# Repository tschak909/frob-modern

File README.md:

# frob-modern: Frob2354

A modern, register-compatible replacement for the **FROB** (Frobco, 1982),
the Apple II card for Atari 2600 development.  The original is 22 74LS
packages and two M58725P 2K x 8 SRAMs; parts that are hard to find today, and
whose modern substitutes make reconstructed boards erratic.  Frob2354 is one
**RP2354B** (RP2350B + 2 MB flash), four 74LVC245A bus buffers, two single
gates and a 3.3 V LDO on an Apple II slot card, with the original's **DIP-24
cable socket** so the existing FROB cable and 2600 cartridge adapter plug
straight in, and the original **register map**, so the existing FROB
software runs unchanged.

```
hardware/   KiCad 10 project (generated from tools/design.py) + JLCPCB outputs
firmware/   Pico SDK firmware: the FROB's RAM and registers, both buses
test/       host tests of the register semantics (the firmware's own code)
```

## Why an RP2354B and not an RP2040

The Apple bus and the 2600 bus run at the same time and are asynchronous to
each other (the 2600 executes from the FROB RAM while the Apple polls the
mailbox), so they cannot share pins.  Apple A0-A7, D0-D7, R/W, /IOSEL,
/DEVSEL, PHI0, /RES plus 2600 A0-A11, /CE, D0-D7 and the buffer controls is
46 GPIOs; the RP2040 has 30.  The RP2350B has 48, 5 V-tolerant pads on
GPIO0-39, the same SDK, and the RP2354B variant carries its flash in the
package.

## The card

* **Apple side:** A0-A7, R/W, /IOSEL, /DEVSEL, PHI0, /RES straight into the
  RP's 5 V-tolerant pads (GP8-20).  D0-D7 through a 74LVC245A whose DIR is
  R/W and whose /OE is `(/IOSEL & /DEVSEL) | A2_DOE` in hardware: the card
  cannot drive the Apple bus outside its own slot cycles.  INT and DMA
  daisy chains are passed through.
* **2600 side (J2, original FROB pin-out):** every cable signal goes through
  a 74LVC245A on the card's 3.3 V (Ioff, 5 V-tolerant), because the 2600 is
  powered separately; 100k pull-downs keep the address inputs defined with
  the cable unplugged.  The data buffer's /OE is `/CE | V_DOE` in hardware.
* **Power:** slot +5 V through a P-FET, USB VBUS through a Schottky, AP2112K
  to 3.3 V.  USB-C is for firmware updates (BOOTSEL) and bench power and can
  never back-feed the Apple.
* 6-layer, 1.6 mm, ENIG with hard-gold bevelled fingers.  All SMD on the top
  side; the DIP-24 socket is hand-soldered (JLCPCB stocks no 24-pin 0.6 in
  socket).

## Documentation

* `firmware/README.md`: register map, how each bus is served, timing
  budget, flashing, bring-up checklist.
* `hardware/README.md`: how the board files are generated and checked, the
  fab outputs, JLCPCB order settings.
* Original hardware, software and manuals: retroabandon/apple2-re `frob/`
  (https://gitlab.com/retroabandon/apple2-re/-/tree/main/frob); MAME's
  `a2frob` device emulates the original.

## Status

Rev0: schematic, 6-layer layout, JLCPCB outputs (`hardware/exports/jlcpcb/`)
and firmware generated and checked -- ERC 0, DRC 0 errors / 0 unconnected /
0 schematic-parity, netlist vs firmware pin map 159/159, host tests of the
register semantics 4144/4144, kicad-happy review triaged in
`hardware/docs/design-review-rev0.md`.
**No board has been built yet** -- see the bring-up checklist in
`firmware/README.md`.

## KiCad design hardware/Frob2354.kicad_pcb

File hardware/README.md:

# Frob2354 hardware

KiCad 10 project.  **Every KiCad file here is generated** from
`tools/design.py` (parts, values, MPN/LCSC codes, every pin's net) and
`tools/placement.py`; edit those and regenerate, not the schematic or board.
The generator toolchain is FujiNet-NES-Rev0's (fujinet-hardware), adapted to
a 6-layer Apple II card.

## Rebuild

Needs KiCad 10 (`kicad-cli` + the `pcbnew` Python module), Python 3 + numpy,
Java and Freerouting 2.4.1 (`~/.local/share/freerouting/freerouting-2.4.1.jar`).

```sh
tools/build_all.sh            # schematic, ERC, netlist checks, BOM, PDF
LAYOUT=1 tools/build_all.sh   # + placement, routing, DRC, gerbers, CPL, renders
```

| step | tool |
|---|---|
| symbols | `harvest_symbols.py` -> `tools/symcache.sexpr` (stock KiCad symbols, flattened) |
| footprints | `make_a2edge_fp.py` (Apple 50-pin edge); the rest are stock KiCad / FujiNet-NES footprints in `Frob2354.pretty` |
| schematic | `gen_sch.py` + `sch_layout.py` + `sch_route.py`: a block-diagram root (Apple slot -> RP2354B -> 2600 cable, power below, joined by buses) and four wired sheets -- parts placed by hand in `sch_layout.py`, every connection drawn by an orthogonal router, parallel buses as KiCad buses, rails as power symbols, signals that leave a sheet as hierarchical labels |
| connectivity | `compare_netlists.py tools/reference-netlist.xml`: the drawing produces exactly the reference connectivity (the netlist only changes when `design.py` does; refresh the reference then) |
| checks | `kicad-cli sch erc`; `check_nets.py`: the netlist against `../firmware/src/frob_pins.h`, the Apple slot pin-out, the original FROB J2 pin-out and the buffer-enable logic -- independent of `design.py` |
| board | `gen_pcb.py` (outline, placement, finger stubs, plane fan-out, RP core copper, zones), `finish_route.py --lock` (RP core corner), `finish_route.py --nets=...` (slot fingers), `route.py` (Freerouting), `via_in_pad.py` (boxed-in RP pins), `drc_fix.py`, `finish_route.py`, `tidy_tracks.py`, `stitch_gnd.py` |
| outputs | `export.py`: BOM, JLCPCB BOM + CPL, gerbers + drill zip, schematic PDF, renders |

## Board

* Apple II peripheral card in the original FROB card's frame (the
  reverse-engineered `a2board.kicad_pcb`): the same 65.4 x 7.62 mm tab, the
  same rear edge; the front is cut back (85.9 x 69.85 mm body).
* Fingers: 0.1 in pitch, 1.52 x 7.32 mm, pins 1-25 on the component side
  (pin 1 toward the front of the computer), 26-50 behind them on the solder
  side, pin N opposite 51-N.  `check_nets.py` asserts this from the footprint.
* Stack-up (FujiNet-NES-Rev0's): F.Cu signals + GND pour / In1 GND / In2 + In3
  signals / In4 +3V3 (DVDD island under the RP2354B core) / B.Cu signals + GND
  pour.  A 4-layer version (two signal layers) was tried first: Freerouting and
  the finisher left ~16 connections open around the RP2354B's 0.4 mm pin rows.
* J2 (FROB cable): DIP-24 0.6 in socket, original pin-out (2732 EPROM order;
  /CE = A12 inverted on the cable adapter, /OE grounded there, pin 24 open).

## Ordering at JLCPCB

`exports/jlcpcb/`: `Frob2354-gerbers.zip`, `BOM-JLCPCB.csv`, `CPL-JLCPCB.csv`.

* PCB: 6 layers, 1.6 mm, **ENIG**, **gold fingers: yes**, **bevelled edge
  (45 deg): yes**, impedance control not needed.  **Via covering: epoxy
  filled and capped (via-in-pad)** -- ten RP2354B signal pads carry a
  0.25/0.15 mm via (`tools/via_in_pad.py`); JLCPCB's 6-layer process includes it.
* Assembly: top side, Economic or Standard; every assembled part has an
  LCSC code (the extended ones: RP2354B, 74LVC245A, 74LVC1G0832, 74LVC1G32,
  AP2112K, AO3401A, USB-C, inductor, crystal, switches).  Check the
  placement preview for pin 1 of U1-U8, the USB-C and the diodes.
* Hand-solder J2: a 24-pin 0.6 in DIP socket (e.g. Mill-Max
  110-43-624-41-001000, or any turned-pin socket).

## Files

| | |
|---|---|
| `Frob2354.kicad_pro/.kicad_sch/.kicad_pcb` | the project (generated) |
| `apple.kicad_sch`, `mcu.kicad_sch`, `vcs.kicad_sch`, `power.kicad_sch` | the four sheets (Apple slot, RP2354B, 2600 cable, power / USB) |
| `tools/relink_pcb.py` | renames board nets / re-points footprints after a schematic redraw, copper untouched (used once, when the drawing became hierarchical: local nets gained sheet paths such as `/mcu/XIN`) |
| `Frob2354.pretty`, `Frob2354.kicad_sym` | project footprints / symbols |
| `datasheets/` | datasheets used in the review (`manifest.json`; PDFs not committed) |
| `docs/` | schematic PDF, layout SVGs, renders |

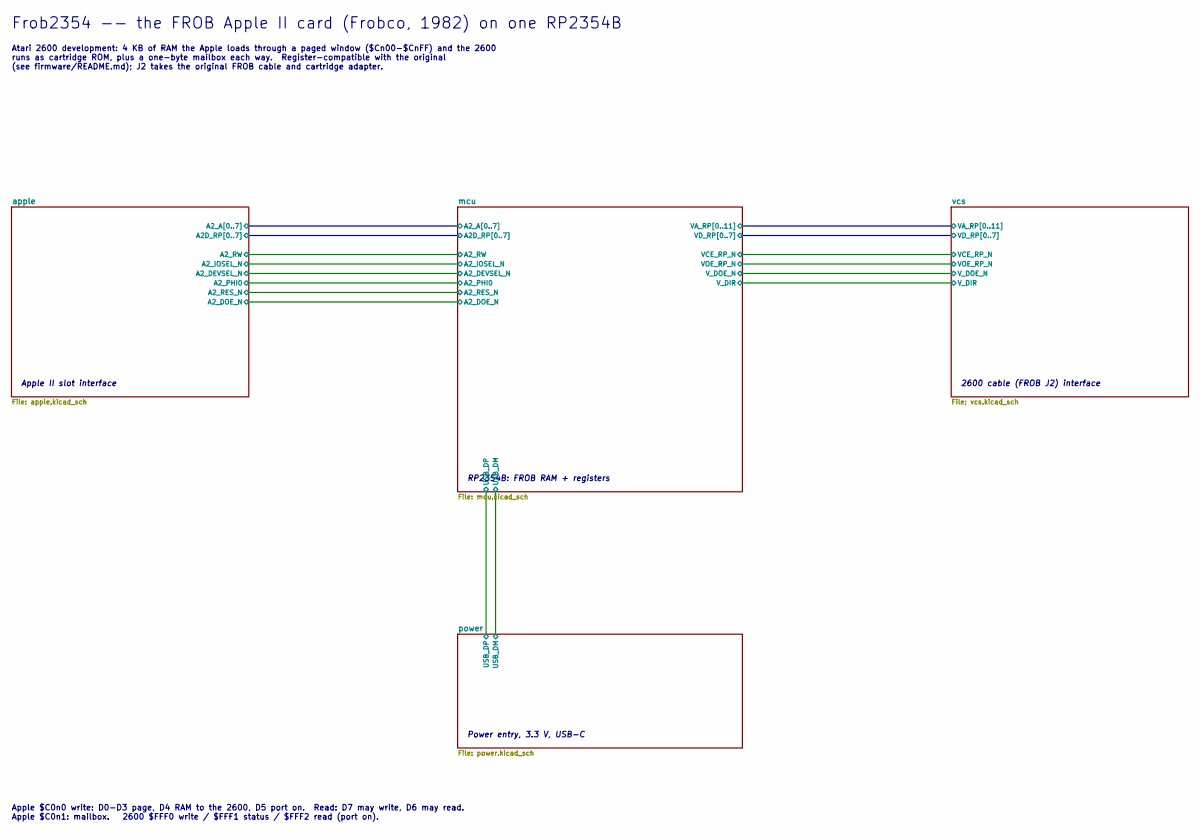
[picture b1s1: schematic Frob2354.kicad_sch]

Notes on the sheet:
Apple II slot interface
RP2354B: FROB RAM + registers
2600 cable (FROB J2) interface
Power entry, 3.3 V, USB-C
Frob2354 -- the FROB Apple II card (Frobco, 1982) on one RP2354B
Atari 2600 development: 4 KB of RAM the Apple loads through a paged window ($Cn00-$CnFF) and the 2600 runs as cartridge ROM, plus a one-byte mailbox each way. Register-compatible with the original (see firmware/README.md); J2 takes the original FROB cable and cartridge adapter.
Apple $C0n0 write: D0-D3 page, D4 RAM to the 2600, D5 port on. Read: D7 may write, D6 may read. Apple $C0n1: mailbox. 2600 $FFF0 write / $FFF1 status / $FFF2 read (port on).

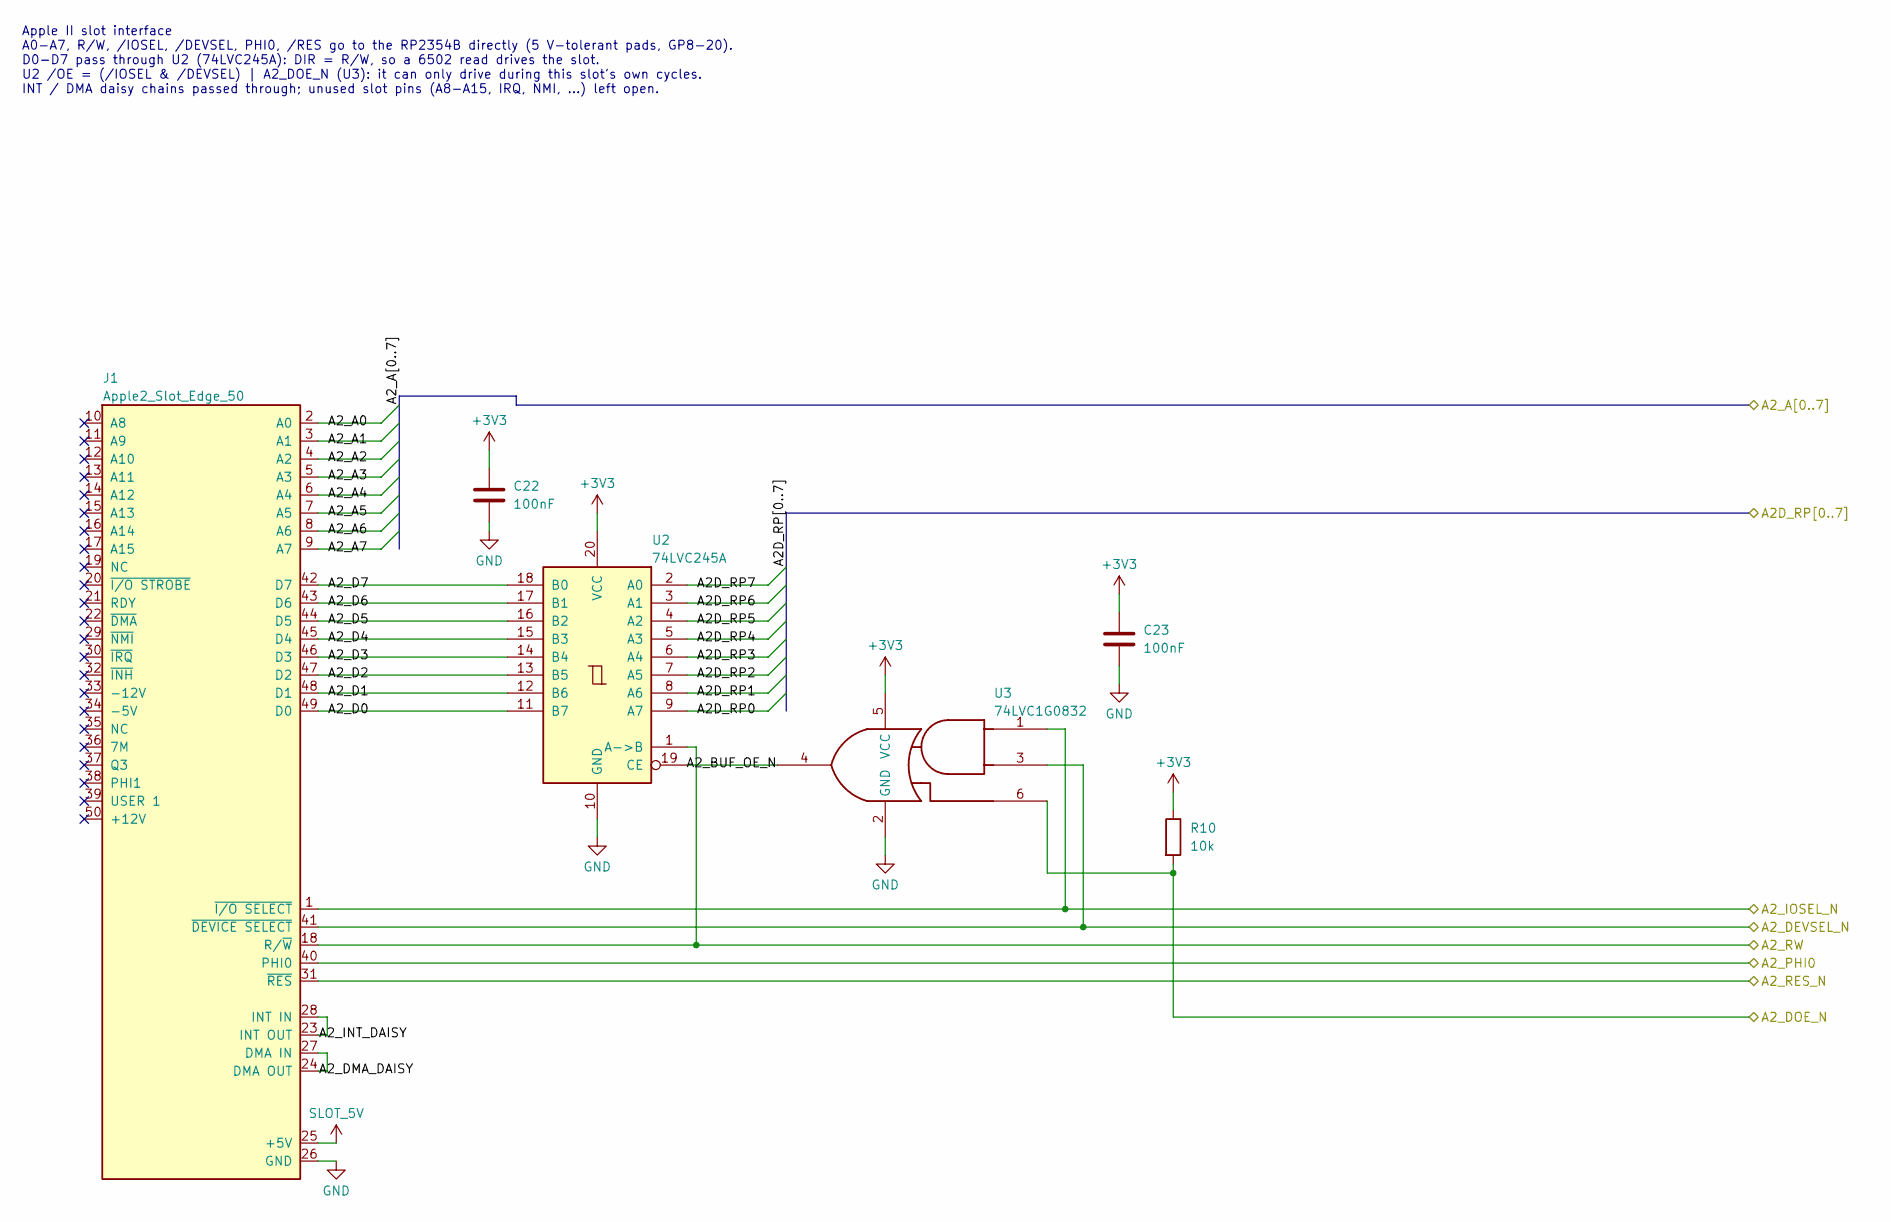
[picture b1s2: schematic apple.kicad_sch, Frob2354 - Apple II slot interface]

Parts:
C22, C23: 100nF; C_0603_1608Metric; MPN CC0603KRX7R9BB104; LCSC C14663
J1: Apple2_Slot_Edge_50
R10: 10k; R_0603_1608Metric; MPN 0603WAF1002T5E; LCSC C25804
U2: 74LVC245A; TSSOP-20_4.4x6.5mm_P0.65mm; MPN SN74LVC245APWR; LCSC C7848
U3: 74LVC1G0832; SOT-23-6; MPN SN74LVC1G0832DBVR; LCSC C206101

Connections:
+3V3: C22.1, C23.1, R10.1, U2.20 (VCC), U3.5 (VCC); also elsewhere on the board
/apple/A2D_RP0: U2.9 (A7); also elsewhere on the board
/apple/A2D_RP1: U2.8 (A6); also elsewhere on the board
/apple/A2D_RP2: U2.7 (A5); also elsewhere on the board
/apple/A2D_RP3: U2.6 (A4); also elsewhere on the board
/apple/A2D_RP4: U2.5 (A3); also elsewhere on the board
/apple/A2D_RP5: U2.4 (A2); also elsewhere on the board
/apple/A2D_RP6: U2.3 (A1); also elsewhere on the board
/apple/A2D_RP7: U2.2 (A0); also elsewhere on the board
/apple/A2_A0: J1.2 (A0); also elsewhere on the board
/apple/A2_A1: J1.3 (A1); also elsewhere on the board
/apple/A2_A2: J1.4 (A2); also elsewhere on the board
/apple/A2_A3: J1.5 (A3); also elsewhere on the board
/apple/A2_A4: J1.6 (A4); also elsewhere on the board
/apple/A2_A5: J1.7 (A5); also elsewhere on the board
/apple/A2_A6: J1.8 (A6); also elsewhere on the board
/apple/A2_A7: J1.9 (A7); also elsewhere on the board
/apple/A2_BUF_OE_N: U2.19 (CE), U3.4
/apple/A2_D0: J1.49 (D0), U2.11 (B7)
/apple/A2_D1: J1.48 (D1), U2.12 (B6)
/apple/A2_D2: J1.47 (D2), U2.13 (B5)
/apple/A2_D3: J1.46 (D3), U2.14 (B4)
/apple/A2_D4: J1.45 (D4), U2.15 (B3)
/apple/A2_D5: J1.44 (D5), U2.16 (B2)
/apple/A2_D6: J1.43 (D6), U2.17 (B1)
/apple/A2_D7: J1.42 (D7), U2.18 (B0)
/apple/A2_DEVSEL_N: J1.41 (~DEVICE SELECT), U3.3; also elsewhere on the board
/apple/A2_DMA_DAISY: J1.24 (DMA OUT), J1.27 (DMA IN)
/apple/A2_DOE_N: R10.2, U3.6; also elsewhere on the board
/apple/A2_INT_DAISY: J1.23 (INT OUT), J1.28 (INT IN)
/apple/A2_IOSEL_N: J1.1 (~I/O SELECT), U3.1; also elsewhere on the board
/apple/A2_PHI0: J1.40 (PHI0); also elsewhere on the board
/apple/A2_RES_N: J1.31 (~RES); also elsewhere on the board
/apple/A2_RW: J1.18 (R/~W), U2.1 (A->B); also elsewhere on the board
GND: C22.2, C23.2, J1.26 (GND), U2.10 (GND), U3.2 (GND); also elsewhere on the board
SLOT_5V: J1.25 (+5V); also elsewhere on the board

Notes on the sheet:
Apple II slot interface A0-A7, R/W, /IOSEL, /DEVSEL, PHI0, /RES go to the RP2354B directly (5 V-tolerant pads, GP8-20). D0-D7 pass through U2 (74LVC245A): DIR = R/W, so a 6502 read drives the slot. U2 /OE = (/IOSEL & /DEVSEL) | A2_DOE_N (U3): it can only drive during this slot's own cycles. INT / D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

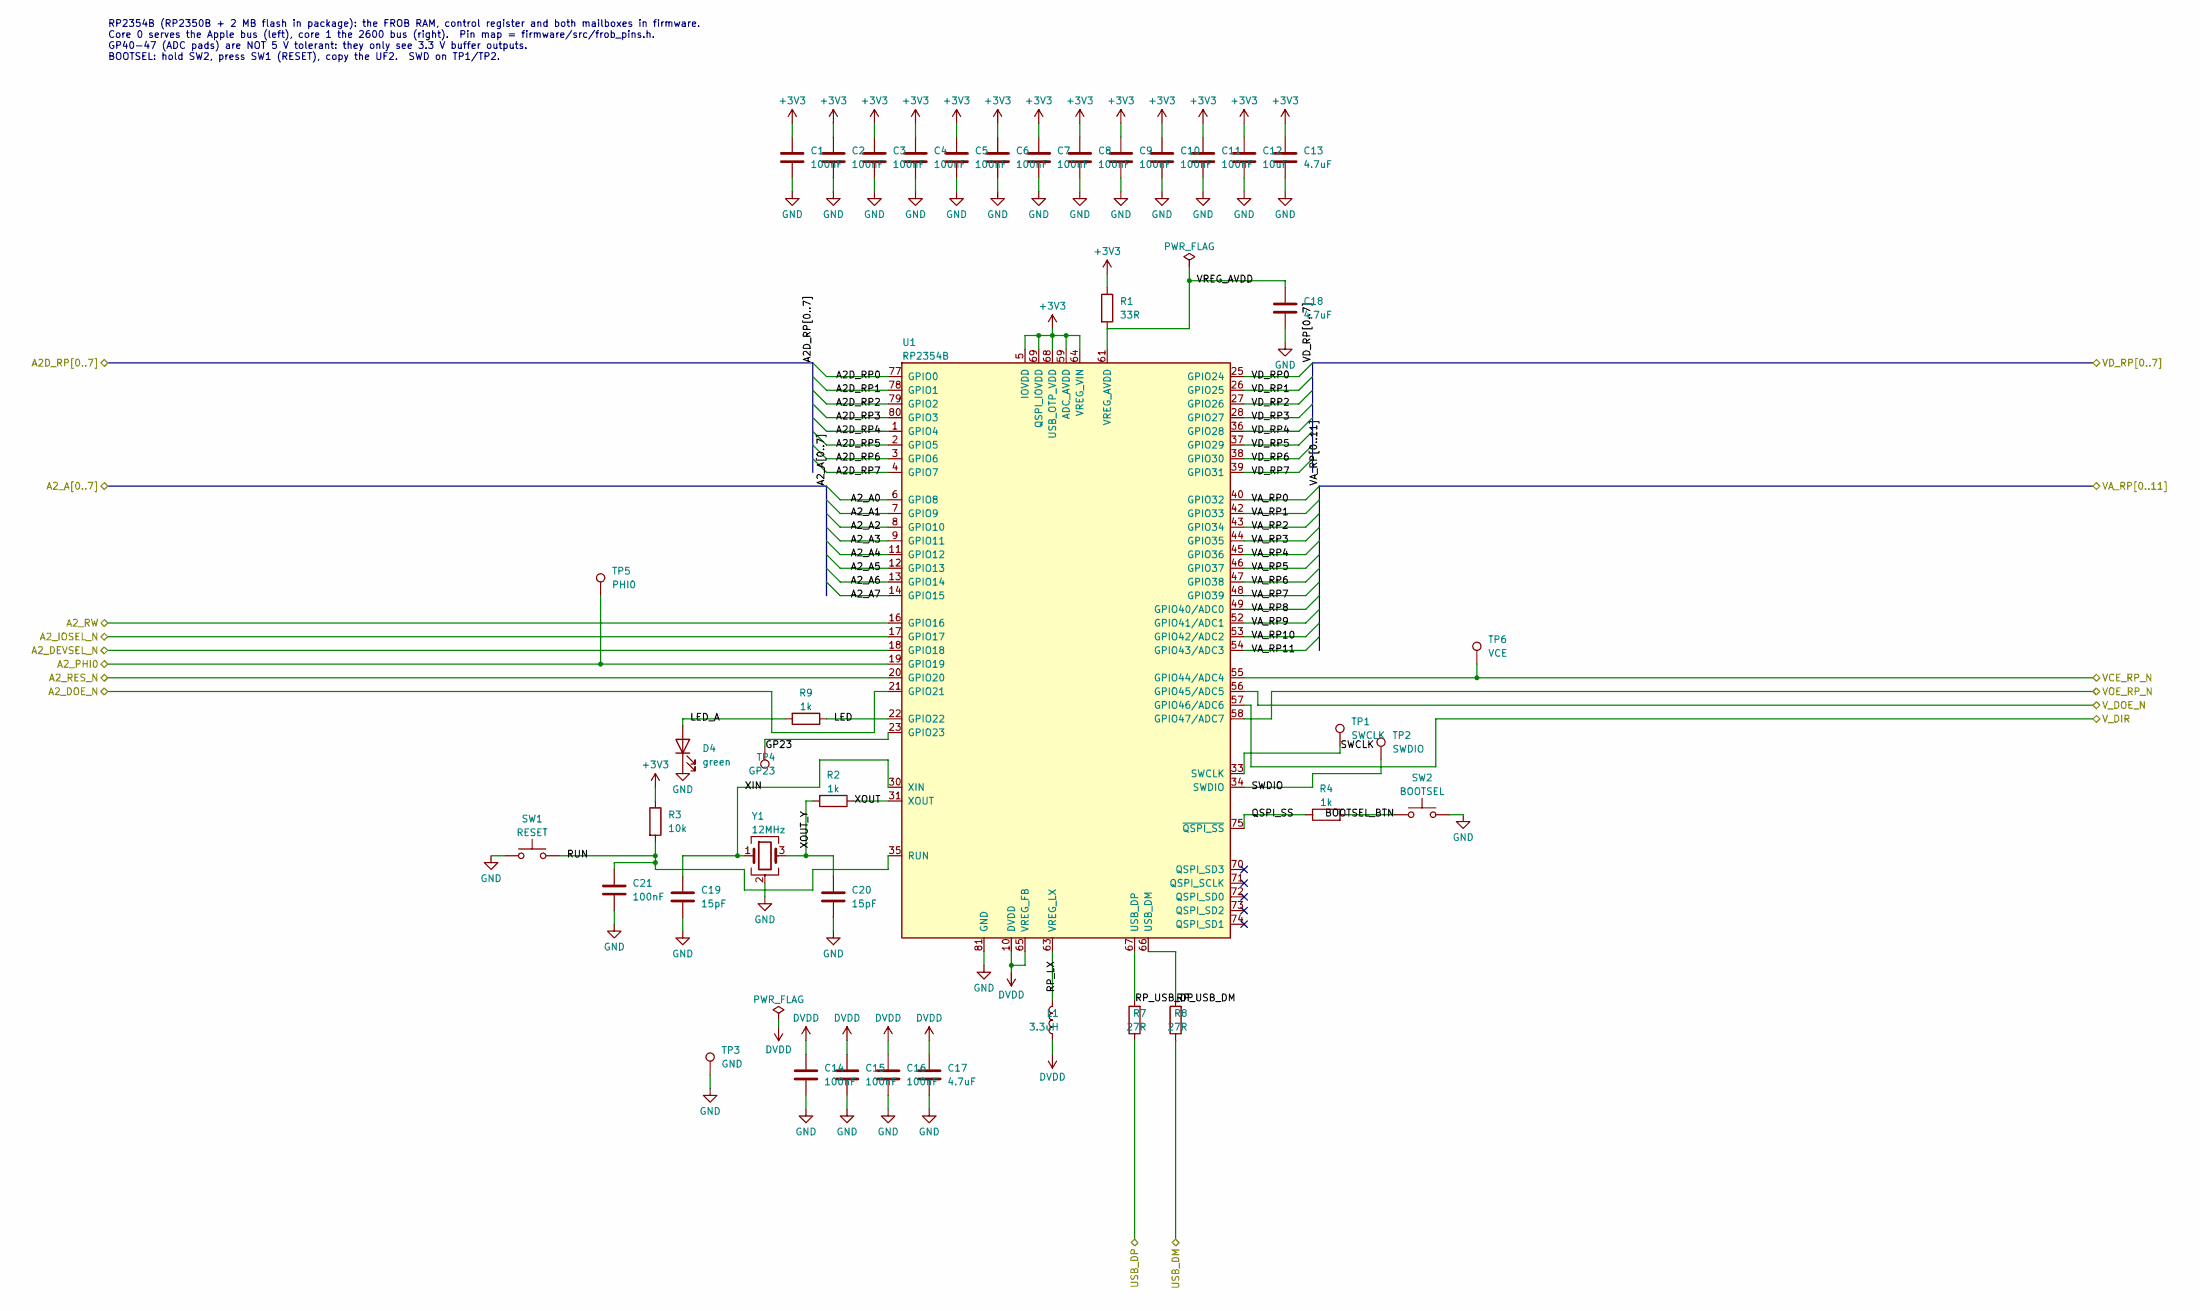
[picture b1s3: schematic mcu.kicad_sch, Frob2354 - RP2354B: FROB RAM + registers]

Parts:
C1, C2, C3, C4, C5, C6, C7, C8, C9, C10, C11, C14, C15, C16, C21: 100nF; C_0603_1608Metric; MPN CC0603KRX7R9BB104; LCSC C14663
C12: 10uF; C_0603_1608Metric; MPN CL10A106KP8NNNC; LCSC C19702
C13, C17, C18: 4.7uF; C_0603_1608Metric; MPN CL10A475KO8NNNC; LCSC C19666
C19, C20: 15pF; C_0603_1608Metric; MPN CL10C150JB8NNNC; LCSC C1644
D4: green; LED_0603_1608Metric; MPN KT-0603G; LCSC C12624
L1: 3.3uH; RPI_L_AOTA-B201610S3R3; MPN AOTA-B201610S3R3-101-T; LCSC C42411119
R1: 33R; R_0603_1608Metric; MPN 0603WAF330JT5E; LCSC C23140
R2, R4, R9: 1k; R_0603_1608Metric; MPN 0603WAF1001T5E; LCSC C21190
R3: 10k; R_0603_1608Metric; MPN 0603WAF1002T5E; LCSC C25804
R7, R8: 27R; R_0603_1608Metric; MPN 0603WAF270JT5E; LCSC C25190
SW1: RESET; SW_SPST_TL3342; MPN TL3342F160QG; LCSC C2886898
SW2: BOOTSEL; SW_SPST_TL3342; MPN TL3342F160QG; LCSC C2886898
TP1: SWCLK; TestPoint_Pad_D1.5mm
TP2: SWDIO; TestPoint_Pad_D1.5mm
TP3: GND; TestPoint_Pad_D1.5mm
TP4: GP23; TestPoint_Pad_D1.5mm
TP5: PHI0; TestPoint_Pad_D1.5mm
TP6: VCE; TestPoint_Pad_D1.5mm
U1: RP2354B; QFN-80-1EP_10x10mm_P0.4mm_EP3.4x3.4mm; MPN RP2354B; LCSC C39843328
Y1: 12MHz; Crystal_SMD_3225-4Pin_3.2x2.5mm; MPN ABM8-272-T3; LCSC C20625731

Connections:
+3V3: C1.1, C2.1, C3.1, C4.1, C5.1, C6.1, C7.1, C8.1, C9.1, C10.1, C11.1, C12.1, C13.1, R1.1, R3.1, U1.5 (IOVDD), U1.15 (IOVDD), U1.24 (IOVDD), U1.29 (IOVDD), U1.41 (IOVDD), U1.50 (IOVDD), U1.59 (ADC_AVDD), U1.60 (IOVDD), U1.64 (VREG_VIN), U1.68 (USB_OTP_VDD), U1.69 (QSPI_IOVDD), U1.76 (IOVDD); also elsewhere on the board
/apple/A2D_RP0: U1.77 (GPIO0); also elsewhere on the board
/apple/A2D_RP1: U1.78 (GPIO1); also elsewhere on the board
/apple/A2D_RP2: U1.79 (GPIO2); also elsewhere on the board
/apple/A2D_RP3: U1.80 (GPIO3); also elsewhere on the board
/apple/A2D_RP4: U1.1 (GPIO4); also elsewhere on the board
/apple/A2D_RP5: U1.2 (GPIO5); also elsewhere on the board
/apple/A2D_RP6: U1.3 (GPIO6); also elsewhere on the board
/apple/A2D_RP7: U1.4 (GPIO7); also elsewhere on the board
/apple/A2_A0: U1.6 (GPIO8); also elsewhere on the board
/apple/A2_A1: U1.7 (GPIO9); also elsewhere on the board
/apple/A2_A2: U1.8 (GPIO10); also elsewhere on the board
/apple/A2_A3: U1.9 (GPIO11); also elsewhere on the board
/apple/A2_A4: U1.11 (GPIO12); also elsewhere on the board
/apple/A2_A5: U1.12 (GPIO13); also elsewhere on the board
/apple/A2_A6: U1.13 (GPIO14); also elsewhere on the board
/apple/A2_A7: U1.14 (GPIO15); also elsewhere on the board
/apple/A2_DEVSEL_N: U1.18 (GPIO18); also elsewhere on the board
/apple/A2_DOE_N: U1.21 (GPIO21); also elsewhere on the board
/apple/A2_IOSEL_N: U1.17 (GPIO17); also elsewhere on the board
/apple/A2_PHI0: TP5.1, U1.19 (GPIO19); also elsewhere on the board
/apple/A2_RES_N: U1.20 (GPIO20); also elsewhere on the board
/apple/A2_RW: U1.16 (GPIO16); also elsewhere on the board
/mcu/BOOTSEL_BTN: R4.2, SW2.1
/mcu/GP23: TP4.1, U1.23 (GPIO23)
/mcu/LED: R9.1, U1.22 (GPIO22)
/mcu/LED_A: D4.2 (A), R9.2
/mcu/QSPI_SS: R4.1, U1.75 (~QSPI_SS)
/mcu/RP_LX: L1.2, U1.63 (VREG_LX)
/mcu/RP_USB_DM: R8.2, U1.66 (USB_DM)
/mcu/RP_USB_DP: R7.2, U1.67 (USB_DP)
/mcu/RUN: C21.1, R3.2, SW1.1, U1.35 (RUN)
/mcu/SWCLK: TP1.1, U1.33 (SWCLK)
/mcu/SWDIO: TP2.1, U1.34 (SWDIO)
/mcu/USB_DM: R8.1; also elsewhere on the board
/mcu/USB_DP: R7.1; also elsewhere on the board
/mcu/VA_RP0: U1.40 (GPIO32); also elsewhere on the board
/mcu/VA_RP1: U1.42 (GPIO33); also elsewhere on the board
/mcu/VA_RP2: U1.43 (GPIO34); also elsewhere on the board
/mcu/VA_RP3: U1.44 (GPIO35); also elsewhere on the board
/mcu/VA_RP4: U1.45 (GPIO36); also elsewhere on the board
/mcu/VA_RP5: U1.46 (GPIO37); also elsewhere on the board
/mcu/VA_RP6: U1.47 (GPIO38); also elsewhere on the board
/mcu/VA_RP7: U1.48 (GPIO39); also elsewhere on the board
/mcu/VA_RP8: U1.49 (GPIO40/ADC0); also elsewhere on the board
/mcu/VA_RP9: U1.52 (GPIO41/ADC1); also elsewhere on the board
/mcu/VA_RP10: U1.53 (GPIO42/ADC2); also elsewhere on the board
/mcu/VA_RP11: U1.54 (GPIO43/ADC3); also elsewhere on the board
/mcu/VCE_RP_N: TP6.1, U1.55 (GPIO44/ADC4); also elsewhere on the board
/mcu/VD_RP0: U1.25 (GPIO24); also elsewhere on the board
/mcu/VD_RP1: U1.26 (GPIO25); also elsewhere on the board
/mcu/VD_RP2: U1.27 (GPIO26); also elsewhere on the board
/mcu/VD_RP3: U1.28 (GPIO27); also elsewhere on the board
/mcu/VD_RP4: U1.36 (GPIO28); also elsewhere on the board
/mcu/VD_RP5: U1.37 (GPIO29); also elsewhere on the board
/mcu/VD_RP6: U1.38 (GPIO30); also elsewhere on the board
/mcu/VD_RP7: U1.39 (GPIO31); also elsewhere on the board
/mcu/VOE_RP_N: U1.58 (GPIO47/ADC7); also elsewhere on the board
/mcu/VREG_AVDD: C18.1, R1.2, U1.61 (VREG_AVDD)
/mcu/V_DIR: U1.57 (GPIO46/ADC6); also elsewhere on the board
/mcu/V_DOE_N: U1.56 (GPIO45/ADC5); also elsewhere on the board
/mcu/XIN: C19.1, U1.30 (XIN), Y1.1
/mcu/XOUT: R2.1, U1.31 (XOUT)
/mcu/XOUT_Y: C20.1, R2.2, Y1.3
DVDD: C14.1, C15.1, C16.1, C17.1, L1.1, U1.10 (DVDD), U1.32 (DVDD), U1.51 (DVDD), U1.65 (VREG_FB)
GND: C1.2, C2.2, C3.2, C4.2, C5.2, C6.2, C7.2, C8.2, C9.2, C10.2, C11.2, C12.2, C13.2, C14.2, C15.2, C16.2, C17.2, C18.2, C19.2, C20.2, C21.2, D4.1 (K), SW1.2, SW2.2, TP3.1, U1.62 (VREG_PGND), U1.81 (GND), Y1.2 (G), Y1.4 (G); also elsewhere on the board

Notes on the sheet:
RP2354B (RP2350B + 2 MB flash in package): the FROB RAM, control register and both mailboxes in firmware. Core 0 serves the Apple bus (left), core 1 the 2600 bus (right). Pin map = firmware/src/frob_pins.h. GP40-47 (ADC pads) are NOT 5 V tolerant: they only see 3.3 V buffer outputs. BOOTSEL: hold S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

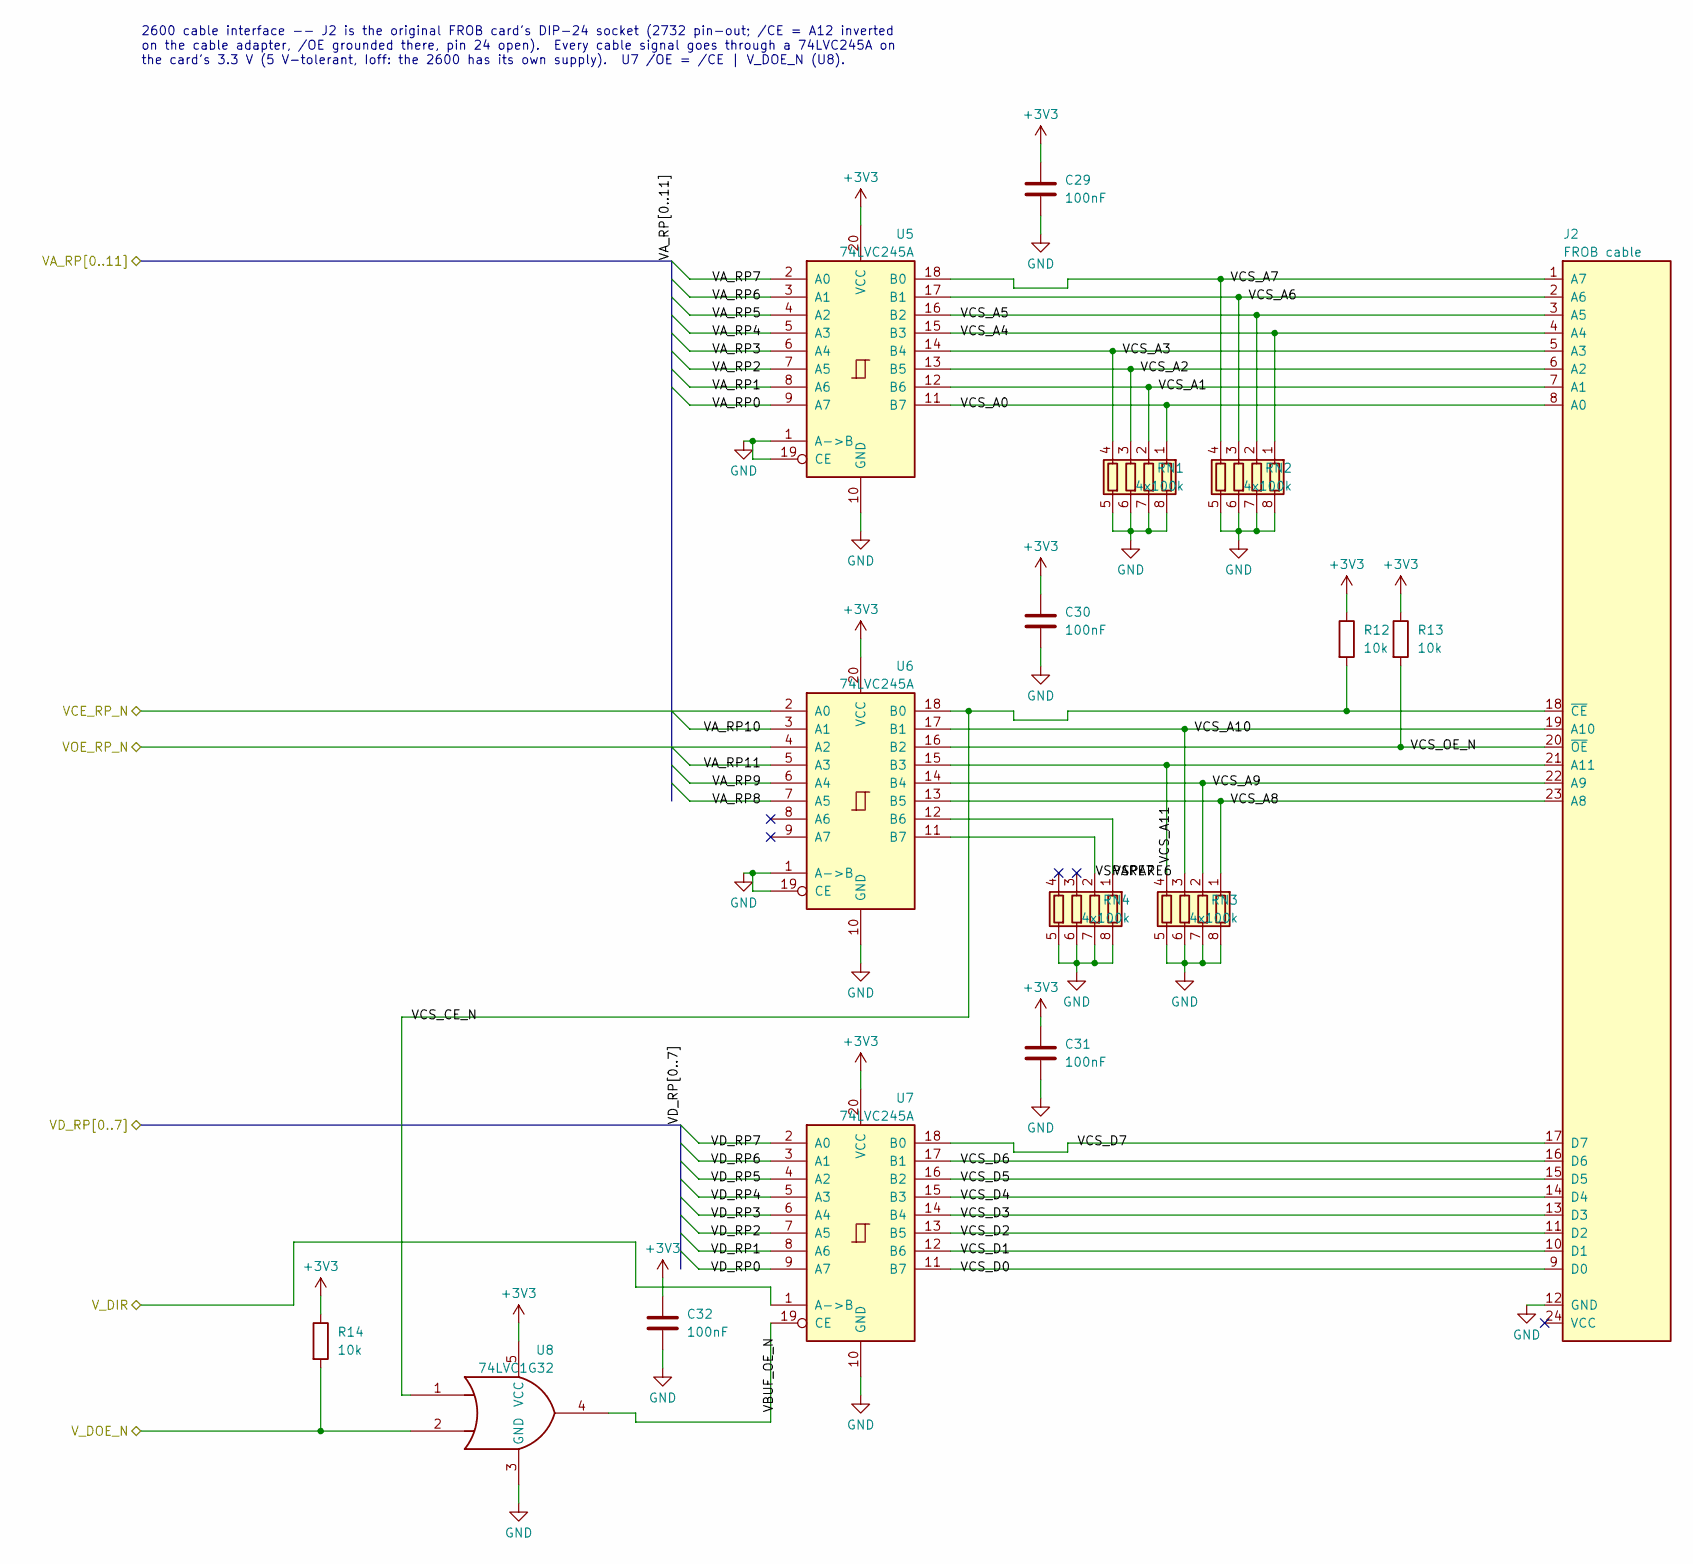
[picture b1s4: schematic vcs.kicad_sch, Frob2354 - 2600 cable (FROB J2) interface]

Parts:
C29, C30, C31, C32: 100nF; C_0603_1608Metric; MPN CC0603KRX7R9BB104; LCSC C14663
J2: FROB cable; DIP-24_W15.24mm_Socket; MPN 110-43-624-41-001000
R12, R13, R14: 10k; R_0603_1608Metric; MPN 0603WAF1002T5E; LCSC C25804
RN1, RN2, RN3, RN4: 4x100k; R_Array_Convex_4x0603; MPN 4D03WGJ0104T5E; LCSC C1996
U5, U6, U7: 74LVC245A; TSSOP-20_4.4x6.5mm_P0.65mm; MPN SN74LVC245APWR; LCSC C7848
U8: 74LVC1G32; SOT-23-5; MPN SN74LVC1G32DBVR; LCSC C10096

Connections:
+3V3: C29.1, C30.1, C31.1, C32.1, R12.1, R13.1, R14.1, U5.20 (VCC), U6.20 (VCC), U7.20 (VCC), U8.5 (VCC); also elsewhere on the board
/mcu/VA_RP0: U5.9 (A7); also elsewhere on the board
/mcu/VA_RP1: U5.8 (A6); also elsewhere on the board
/mcu/VA_RP2: U5.7 (A5); also elsewhere on the board
/mcu/VA_RP3: U5.6 (A4); also elsewhere on the board
/mcu/VA_RP4: U5.5 (A3); also elsewhere on the board
/mcu/VA_RP5: U5.4 (A2); also elsewhere on the board
/mcu/VA_RP6: U5.3 (A1); also elsewhere on the board
/mcu/VA_RP7: U5.2 (A0); also elsewhere on the board
/mcu/VA_RP8: U6.7 (A5); also elsewhere on the board
/mcu/VA_RP9: U6.6 (A4); also elsewhere on the board
/mcu/VA_RP10: U6.3 (A1); also elsewhere on the board
/mcu/VA_RP11: U6.5 (A3); also elsewhere on the board
/mcu/VCE_RP_N: U6.2 (A0); also elsewhere on the board
/mcu/VD_RP0: U7.9 (A7); also elsewhere on the board
/mcu/VD_RP1: U7.8 (A6); also elsewhere on the board
/mcu/VD_RP2: U7.7 (A5); also elsewhere on the board
/mcu/VD_RP3: U7.6 (A4); also elsewhere on the board
/mcu/VD_RP4: U7.5 (A3); also elsewhere on the board
/mcu/VD_RP5: U7.4 (A2); also elsewhere on the board
/mcu/VD_RP6: U7.3 (A1); also elsewhere on the board
/mcu/VD_RP7: U7.2 (A0); also elsewhere on the board
/mcu/VOE_RP_N: U6.4 (A2); also elsewhere on the board
/mcu/V_DIR: U7.1 (A->B); also elsewhere on the board
/mcu/V_DOE_N: R14.2, U8.2; also elsewhere on the board
/vcs/VBUF_OE_N: U7.19 (CE), U8.4
/vcs/VCS_A0: J2.8 (A0), RN1.1 (R1.1), U5.11 (B7)
/vcs/VCS_A1: J2.7 (A1), RN1.2 (R2.1), U5.12 (B6)
/vcs/VCS_A2: J2.6 (A2), RN1.3 (R3.1), U5.13 (B5)
/vcs/VCS_A3: J2.5 (A3), RN1.4 (R4.1), U5.14 (B4)
/vcs/VCS_A4: J2.4 (A4), RN2.1 (R1.1), U5.15 (B3)
/vcs/VCS_A5: J2.3 (A5), RN2.2 (R2.1), U5.16 (B2)
/vcs/VCS_A6: J2.2 (A6), RN2.3 (R3.1), U5.17 (B1)
/vcs/VCS_A7: J2.1 (A7), RN2.4 (R4.1), U5.18 (B0)
/vcs/VCS_A8: J2.23 (A8), RN3.1 (R1.1), U6.13 (B5)
/vcs/VCS_A9: J2.22 (A9), RN3.2 (R2.1), U6.14 (B4)
/vcs/VCS_A10: J2.19 (A10), RN3.3 (R3.1), U6.17 (B1)
/vcs/VCS_A11: J2.21 (A11), RN3.4 (R4.1), U6.15 (B3)
/vcs/VCS_CE_N: J2.18 (~CE), R12.2, U6.18 (B0), U8.1
/vcs/VCS_D0: J2.9 (D0), U7.11 (B7)
/vcs/VCS_D1: J2.10 (D1), U7.12 (B6)
/vcs/VCS_D2: J2.11 (D2), U7.13 (B5)
/vcs/VCS_D3: J2.13 (D3), U7.14 (B4)
/vcs/VCS_D4: J2.14 (D4), U7.15 (B3)
/vcs/VCS_D5: J2.15 (D5), U7.16 (B2)
/vcs/VCS_D6: J2.16 (D6), U7.17 (B1)
/vcs/VCS_D7: J2.17 (D7), U7.18 (B0)
/vcs/VCS_OE_N: J2.20 (~OE), R13.2, U6.16 (B2)
/vcs/VSPARE6: RN4.1 (R1.1), U6.12 (B6)
/vcs/VSPARE7: RN4.2 (R2.1), U6.11 (B7)
GND: C29.2, C30.2, C31.2, C32.2, J2.12 (GND), RN1.5 (R4.2), RN1.6 (R3.2), RN1.7 (R2.2), RN1.8 (R1.2), RN2.5 (R4.2), RN2.6 (R3.2), RN2.7 (R2.2), RN2.8 (R1.2), RN3.5 (R4.2), RN3.6 (R3.2), RN3.7 (R2.2), RN3.8 (R1.2), RN4.5 (R4.2), RN4.6 (R3.2), RN4.7 (R2.2), RN4.8 (R1.2), U5.1 (A->B), U5.10 (GND), U5.19 (CE), U6.1 (A->B), U6.10 (GND), U6.19 (CE), U7.10 (GND), U8.3 (GND); also elsewhere on the board

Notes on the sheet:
2600 cable interface -- J2 is the original FROB card's DIP-24 socket (2732 pin-out; /CE = A12 inverted on the cable adapter, /OE grounded there, pin 24 open). Every cable signal goes through a 74LVC245A on the card's 3.3 V (5 V-tolerant, Ioff: the 2600 has its own supply). U7 /OE = /CE | V_DOE_N (U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

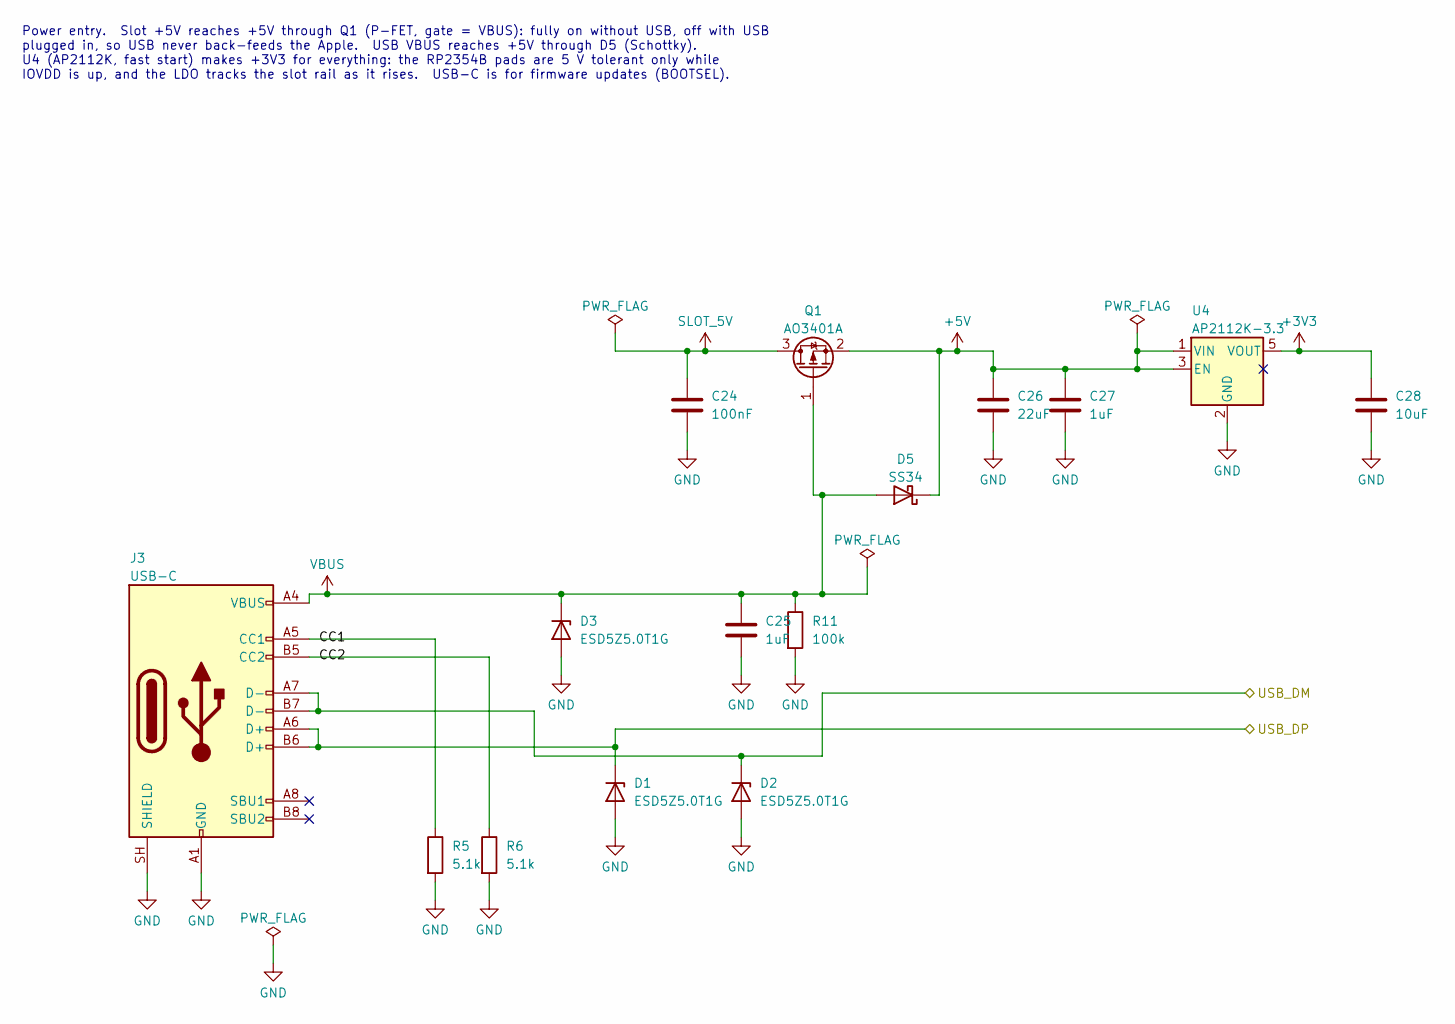
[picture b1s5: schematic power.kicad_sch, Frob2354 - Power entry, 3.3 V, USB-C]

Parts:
C24: 100nF; C_0603_1608Metric; MPN CC0603KRX7R9BB104; LCSC C14663
C25, C27: 1uF; C_0603_1608Metric; MPN CL10A105KB8NNNC; LCSC C15849
C26: 22uF; C_0805_2012Metric; MPN CL21A226MAQNNNE; LCSC C45783
C28: 10uF; C_0603_1608Metric; MPN CL10A106KP8NNNC; LCSC C19702
D1, D2, D3: ESD5Z5.0T1G; D_SOD-523; MPN ESD5Z5.0T1G; LCSC C82044
D5: SS34; D_SMA; MPN SS34; LCSC C8678
J3: USB-C; USB_C_Receptacle_HRO_TYPE-C-31-M-12; MPN TYPE-C-31-M-12; LCSC C165948
Q1: AO3401A; SOT-23; MPN AO3401A; LCSC C15127
R5, R6: 5.1k; R_0603_1608Metric; MPN 0603WAF5101T5E; LCSC C23186
R11: 100k; R_0603_1608Metric; MPN 0603WAF1003T5E; LCSC C25803
U4: AP2112K-3.3; SOT-23-5; MPN AP2112K-3.3TRG1; LCSC C51118

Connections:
+3V3: C28.1, U4.5 (VOUT); also elsewhere on the board
+5V: C26.1, C27.1, D5.1 (K), Q1.2 (S), U4.1 (VIN), U4.3 (EN)
/mcu/USB_DM: D2.1 (K), J3.A7 (D-), J3.B7 (D-); also elsewhere on the board
/mcu/USB_DP: D1.1 (K), J3.A6 (D+), J3.B6 (D+); also elsewhere on the board
/power/CC1: J3.A5 (CC1), R5.1
/power/CC2: J3.B5 (CC2), R6.1
GND: C24.2, C25.2, C26.2, C27.2, C28.2, D1.2 (A), D2.2 (A), D3.2 (A), J3.A1 (GND), J3.A12 (GND), J3.B1 (GND), J3.B12 (GND), J3.SH (SHIELD), R5.2, R6.2, R11.2, U4.2 (GND); also elsewhere on the board
SLOT_5V: C24.1, Q1.3 (D); also elsewhere on the board
VBUS: C25.1, D3.1 (K), D5.2 (A), J3.A4 (VBUS), J3.A9 (VBUS), J3.B4 (VBUS), J3.B9 (VBUS), Q1.1 (G), R11.1

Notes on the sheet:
Power entry. Slot +5V reaches +5V through Q1 (P-FET, gate = VBUS): fully on without USB, off with USB plugged in, so USB never back-feeds the Apple. USB VBUS reaches +5V through D5 (Schottky). U4 (AP2112K, fast start) makes +3V3 for everything: the RP2354B pads are 5 V tolerant only while IOVDD is 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
